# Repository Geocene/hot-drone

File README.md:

# Mechanical 
## CAD
Onshape files are [here](https://cad.onshape.com/documents/938009ca848e8f70363ec877/w/f0bb0f5f0f71f81ef3c97b4d/e/251c57603ced91541ac1788a). This project is fairly messy with lots of different iterations and bad naming conventions. Not fit for human consumption, but it's there. 

## Dampers
We use 2 kinds of dampers. 
1. "Goo ball" dampers from the [DJI Matrice/Inspire series](https://www.terrestrialimaging.com/products/dji-matrice-200-300-series-rubber-damper?srsltid=AfmBOopQN6PGU1pUkCl2peEYZ-s4ZuK-9KpNYBQmUYXlq-m3I-rZX4Zd). Note that these take a bit of force for installation, and they can be easily torn during installation or disassebly. Use caution. 
2. Camera gimbal dampers from the DJI Mini Pro 4. Note that we only use the side with 3 "posts." Purchased [here](https://www.amazon.com/dp/B0CZJTMX98?ref_=ppx_hzsearch_conn_dt_b_fed_asin_title_1&th=1). The #2 thread forming screws are used as the bosses to connect the damper to the camera holder. For these to work, leave about a 0.5mm gap (don't screw them all the way down). After installing, cut excess pull tab. 

## Printing
Prints were made on a Bambu H2D out of both PLA and PETG. Both seemed to work fine, so the majority of parts were made from faster/cheaper PLA. Orientation was the Bambu Studio default for each part. Supports are necessary for all parts. Printing all the parts requires at least 2 plates on the H2D. 

Bambu Studio file is in the repo.

## Fasteners
The top "spider" damper requires [heat set inserts](https://www.amazon.com/ruthex-M3-Threaded-Inserts-RX-M3x5-7/dp/B08BCRZZS3/ref=sr_1_1_sspa?dib=eyJ2IjoiMSJ9.CYXB_0oopeIbtnzM2jaWJOhp5CdSJT4SrxoRYNbWBGoz2BCay_MDXh4nX70ZgaBIDdVodtFxVVowoT_KhBIy4wQeFE5IE9mUfYH0m4mKqX2vG0iHHmSGIKdzsXj92ehltR5wSSOtZ7xIB9UUP7ZU__k5VXXv0UWUoDS2Rq5ES-pIgGob0wZzE3PrtbQTAjnfmdfqT1ne7lT6iKSrc7jFOFcIASh5mShtVlbXu1bD0iw.VmIUA6fNe0WOZTDa9YbKId9nPjEPwrSBlhP9Y2QhM-M&dib_tag=se&keywords=m3+inserts&qid=1756918881&sr=8-1-spons&sp_csd=d2lkZ2V0TmFtZT1zcF9hdGY&psc=1).

#2x3/16" trilobe [threadforming screws](https://www.mcmaster.com/99461A710/) were used to attach the Raspberry Pis and the camera modules to their prints

#2x3/8" trilobe [threadforming screws](https://www.mcmaster.com/99461A725/) were used to attach the camera holder cantilevers to the bottom damper spider. 

[M3x8 cap screws](https://www.mcmaster.com/92095A181/) were used to attach the top spider damper to the drone. 

The same Holybro-supplied M2.5 screws that held the aesthetic "caps" onto the rotors are reused to attach the new landing gear.

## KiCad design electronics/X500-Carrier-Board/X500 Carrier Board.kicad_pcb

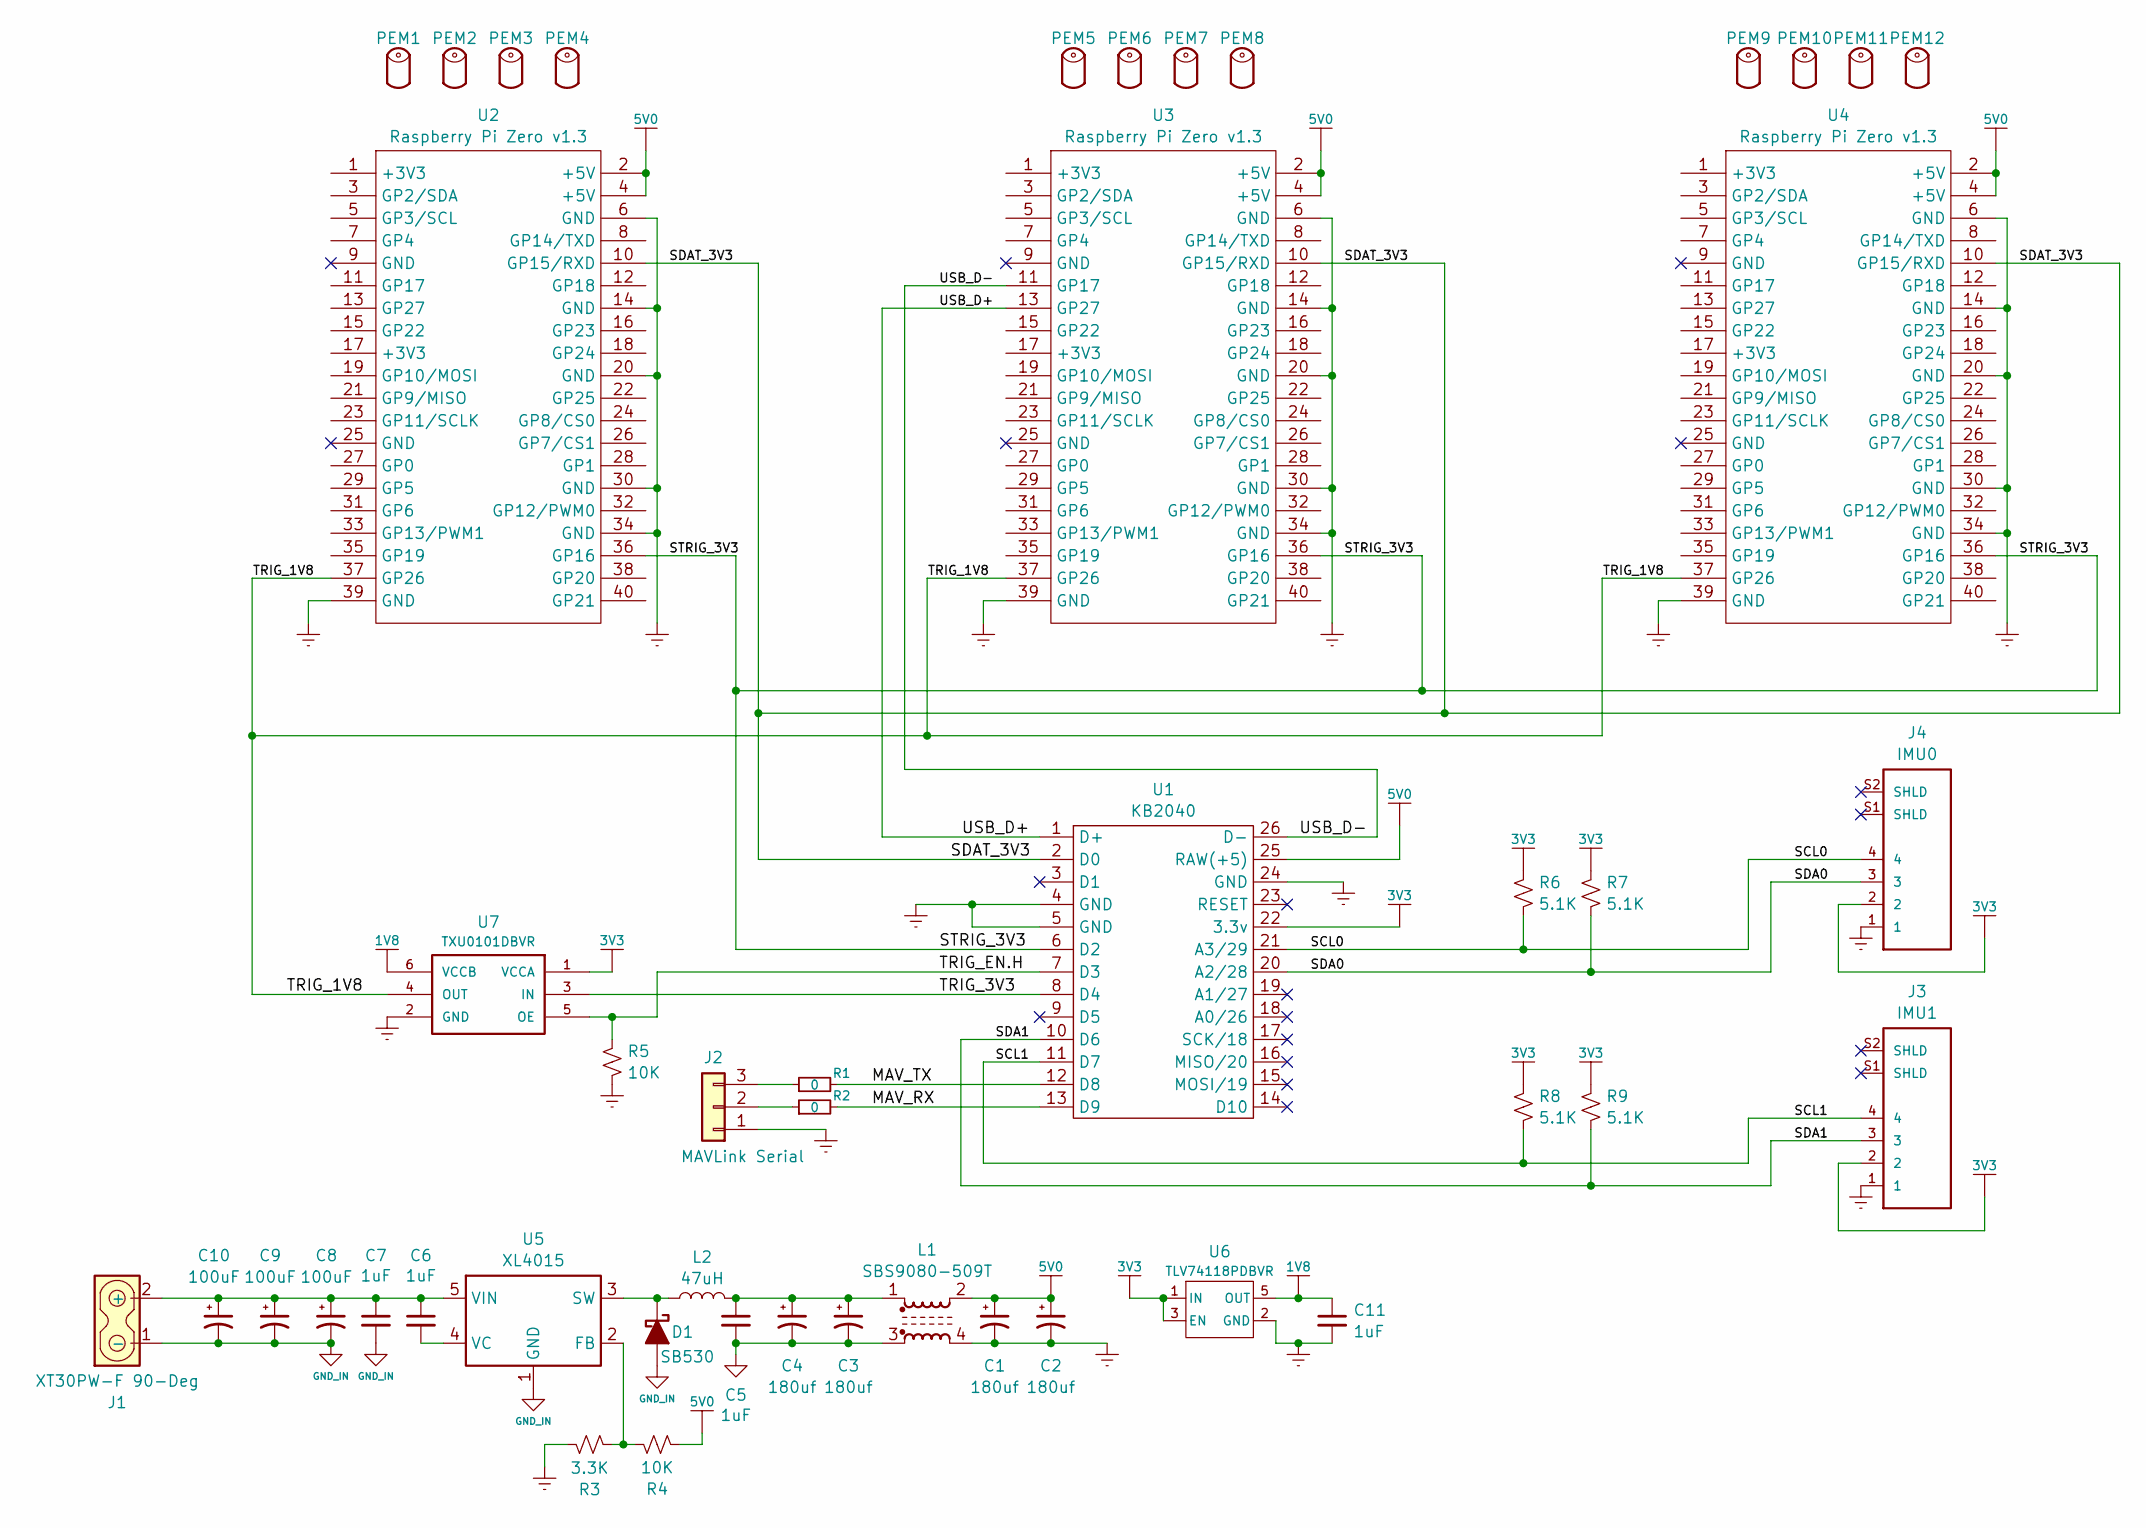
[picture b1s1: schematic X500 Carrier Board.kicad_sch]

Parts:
C1, C2, C3, C4: 180uf; CP_Elec_6.3x5.7; MPN RSA1C181MCN1GS
C5, C6, C7, C11: 1uF; C_0603_1608Metric; MPN CGA3E1X7R1V105K080AE
C8, C9, C10: 100uF; CP_Elec_6.6x5.8; MPN HHXJ250ARA101MF61G
D1: SB530; D_DO-201AD_P15.24mm_Horizontal; MPN SB530-E3/54
J1: XT30PW-F 90-Deg; AMASS_XT30PW-F_1x02_P2.50mm_Horizontal
J2: MAVLink Serial; JST_GH_SM03B-GHS-TB_1x03-1MP_P1.25mm_Horizontal
J3: IMU1; GCT_FFC3B07-04-T; MPN FFC3B07-04-T
J4: IMU0; GCT_FFC3B07-04-T; MPN FFC3B07-04-T
L1: SBS9080-509T; KEMET SBS9080-509T
L2: 47uH; L_TechFuse_SL1265; MPN 2100LL-470-H-RC
PEM1, PEM2, PEM3, PEM4, PEM5, PEM6, PEM7, PEM8, PEM9, PEM10, PEM11, PEM12: SMTSO-M25-6ET; PEM SMTSO-M25-6ET (SS Only); MPN SMTSO-M25-6ET
R1, R2: 0; R_Axial_DIN0204_L3.6mm_D1.6mm_P5.08mm_Horizontal; MPN CD18ZT0R00
R3: 3.3K; R_0603_1608Metric; MPN RMCF0603FT3K30
R4, R5: 10K; R_0603_1608Metric; MPN RMCF0603FT10K0
R6, R7, R8, R9: 5.1K; R_0603_1608Metric; MPN RMCF0603FT5K10
U1: KB2040; Adafruit KB2040_SMT
U2, U3, U4: Raspberry Pi Zero v1.3; RASPI_ZERO_2W (No TPs)
U5: XL4015; TO-263-5_TabPin3
U6: TLV74118PDBVR; DBV0005A; MPN TLV74118PDBVR
U7: TXU0101DBVR; DBV0006A; MPN TXU0101DBVR

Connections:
1V8: C11.1, U6.5 (OUT), U7.6 (VCCB)
3V3: J3.2, J4.2, R6.1, R7.1, R8.1, R9.1, U1.22 (3.3v), U6.1 (IN), U6.3 (EN), U7.1 (VCCA)
5V0: C1.1, C2.1, L1.2, R4.1, U1.25 (RAW(+5)), U2.2 (+5V), U2.4 (+5V), U3.2 (+5V), U3.4 (+5V), U4.2 (+5V), U4.4 (+5V)
/MAV_RX: R2.2, U1.13 (D9)
/MAV_TX: R1.2, U1.12 (D8)
/SCL0: J4.4, R6.2, U1.21 (A3/29)
/SCL1: J3.4, R8.2, U1.11 (D7)
/SDA0: J4.3, R7.2, U1.20 (A2/28)
/SDA1: J3.3, R9.2, U1.10 (D6)
/SDAT_3V3: U1.2 (D0), U2.10 (GP15/RXD), U3.10 (GP15/RXD), U4.10 (GP15/RXD)
/STRIG_3V3: U1.6 (D2), U2.36 (GP16), U3.36 (GP16), U4.36 (GP16)
/TRIG_1V8: U2.37 (GP26), U3.37 (GP26), U4.37 (GP26), U7.4 (OUT)
/TRIG_3V3: U1.8 (D4), U7.3 (IN)
/TRIG_EN.H: R5.1, U1.7 (D3), U7.5 (OE)
/USB_D+: U1.1 (D+), U3.13 (GP27)
/USB_D-: U1.26 (D-), U3.11 (GP17)
GND: C1.2, C2.2, C11.2, J2.1, J3.1, J4.1, L1.4, R3.2, R5.2, U1.4 (GND), U1.5 (GND), U1.24 (GND), U2.6 (GND), U2.14 (GND), U2.20 (GND), U2.30 (GND), U2.34 (GND), U2.39 (GND), U3.6 (GND), U3.14 (GND), U3.20 (GND), U3.30 (GND), U3.34 (GND), U3.39 (GND), U4.6 (GND), U4.14 (GND), U4.20 (GND), U4.30 (GND), U4.34 (GND), U4.39 (GND), U6.2 (GND), U7.2 (GND)
GND_IN: C3.2, C4.2, C5.2, C7.2, C8.2, C9.2, C10.2, D1.2 (A), J1.1 (-), L1.3, U5.1 (GND)
unnamed: C3.1, C4.1, C5.1, L1.1, L2.2
unnamed: D1.1 (K), L2.1, U5.3 (SW)
unnamed: C6.1, C7.1, C8.1, C9.1, C10.1, J1.2 (+), U5.5 (VIN)
unnamed: J2.2, R2.1
unnamed: J2.3, R1.1
unnamed: R3.1, R4.2, U5.2 (FB)
unnamed: C6.2, U5.4 (VC)

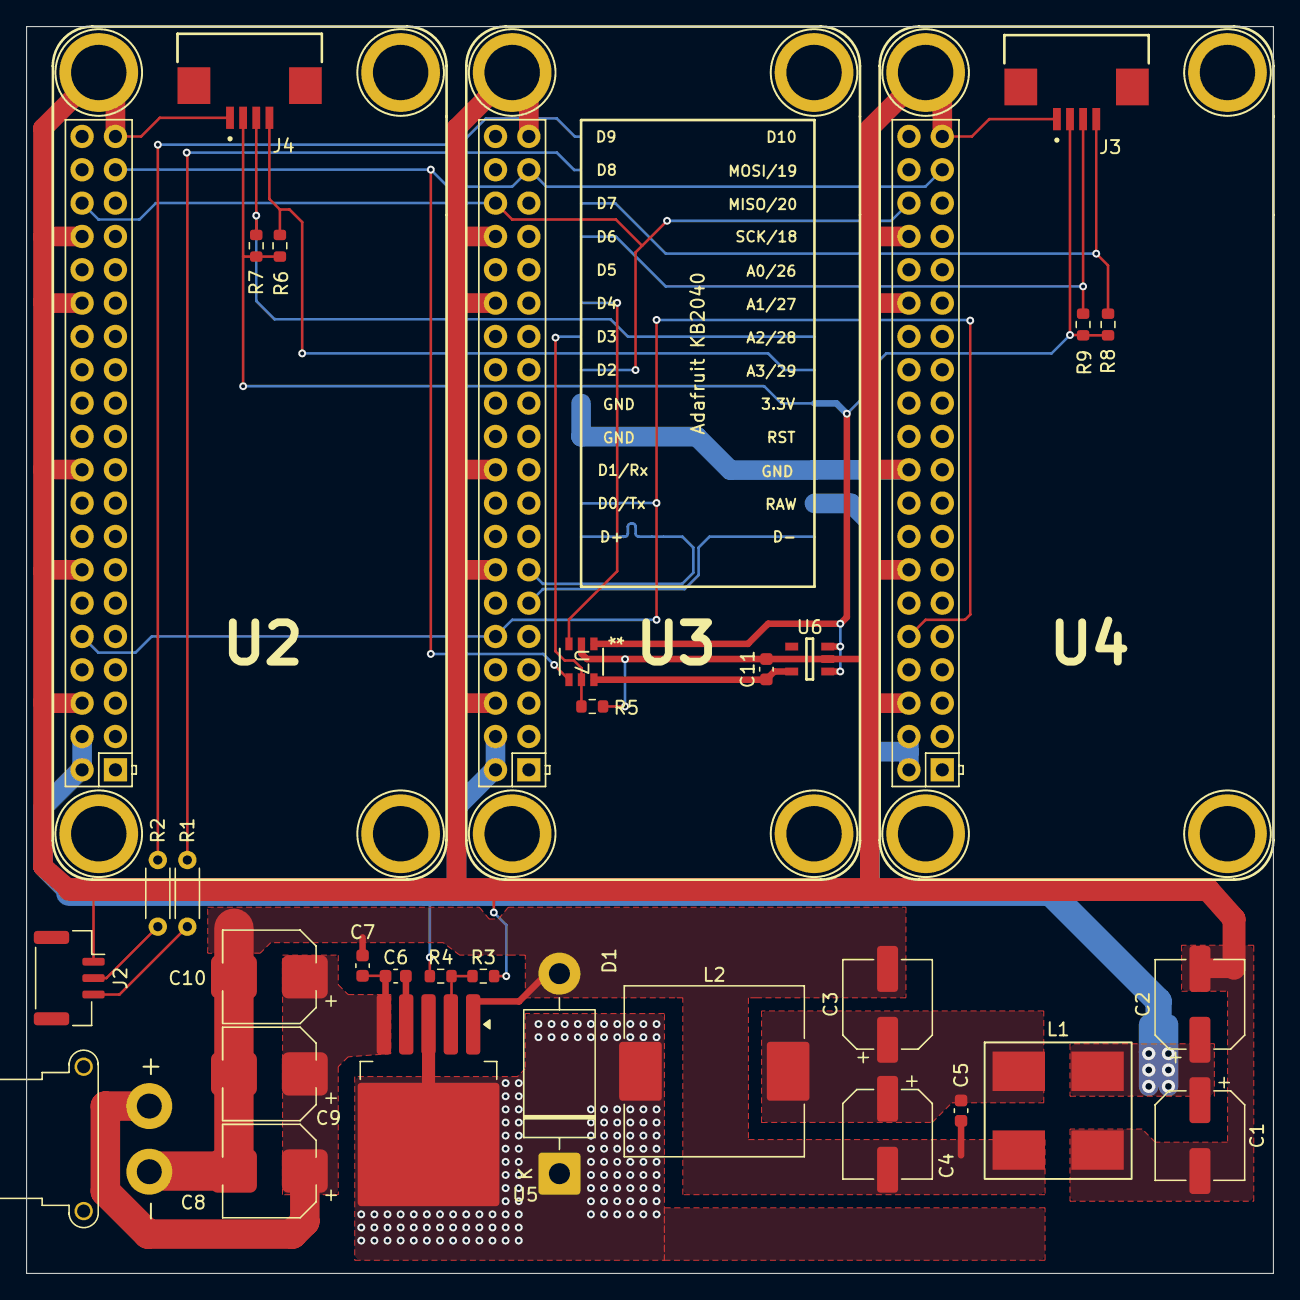
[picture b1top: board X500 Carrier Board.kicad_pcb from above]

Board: 2 copper layers, 95.0 x 95.0 mm, 46 parts (1 on the bottom side), 25 nets.

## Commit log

2025-09-02 adding 3D print files
2025-09-03 adding bambu studio
2025-09-03 adding STEP files
2025-09-05 Get some files for camera computers and post-processing into git.
2025-09-05 Early README and current flight computer params.
2025-09-05 Ignore Python cache files in software.
2025-09-05 Relocate 3d print files to be under X500v2 vehicle.
    Add a pointer from the vehicle's README.
2025-09-05 Commit of my hacky 4.5 kHz accelerometer data logger.
2025-09-08 X500 V2 component list, FC port use and flight modes, a few TODOs,
2025-09-08 A start on camera computer documentation
    Mostly hardware, since in the short term, I'm hoping to hand over an SD card image and a few simple tweaks and call it a day.
2025-09-10 A few more blobs of documentation, from topics of discussion today.
2025-09-19 Document Raspberry Pi regulators.
2025-09-19 Add detail on Raspberry Pi 5 regulator choice.
2025-09-19 Add image of Raspberry Pi with heat sink and battery.
    Also link to vehicle documentation on how the voltage regulators are attached.
2025-09-19 Doc: Vehicle: links to sub-sections.
2025-09-19 Doc: Vehicle: Added propeller testing, rationale, such as it is.
2025-09-19 Doc: Vehicle: Image of camera system mess.
    I could get a better picture, but... later.
2025-10-04 3-Oct-25 version of the Pi Zero carrier & STEP of full X500 assy with numerous tweaks
2025-10-13 Reorganize data logger code for Zero-era timing nexus functionality.
2025-10-23 Massive changes for new triple Pi Zero 2 W architecture.
2025-10-28 Add a camera capture counter to the USB payload.
2025-11-01 More large changes to camera computer code for 3 x Pi Zero configuration.
2025-11-01 Tweaks to BUILD and INSTALL.
2025-11-01 Specify working directory
    GPIO library notify function was trying to drop its notify fd in `/`.
2025-11-01 Oops, need to chown the `~/out` directory.
2025-11-01 Alter push.sh to take host name instead of having to edit file.
